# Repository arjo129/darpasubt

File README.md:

# net/batman-doc
Document all things related to batman.

## Network Bridges
A network bridge is a virtual cable, that connects two network interfaces.

By default, OpenWrt puts `eth0` and `wlan0` on the same bridge. This allows
connections on `wlan0` to connect over `eth0`. If `eth0` is connected to the
internet, then `wlan0` is connected to the internet.
```
root@OpenWrt:~# brctl show
bridge name     bridge id               STP enabled     interfaces
br-lan          7fff.b827eb551e8a       no              eth0
                                                        wlan0
```

## SSH over IPv6
It is possible to SSH from device A into an IPv6 device B, if batman is running 
on device B. I suspect this is because a layer 2 protocol needs to be running 
in order for SSH over IPv6 to work.

The SSH command is:
```
ssh -6 <user>@<device B address>%<device A interface>
```

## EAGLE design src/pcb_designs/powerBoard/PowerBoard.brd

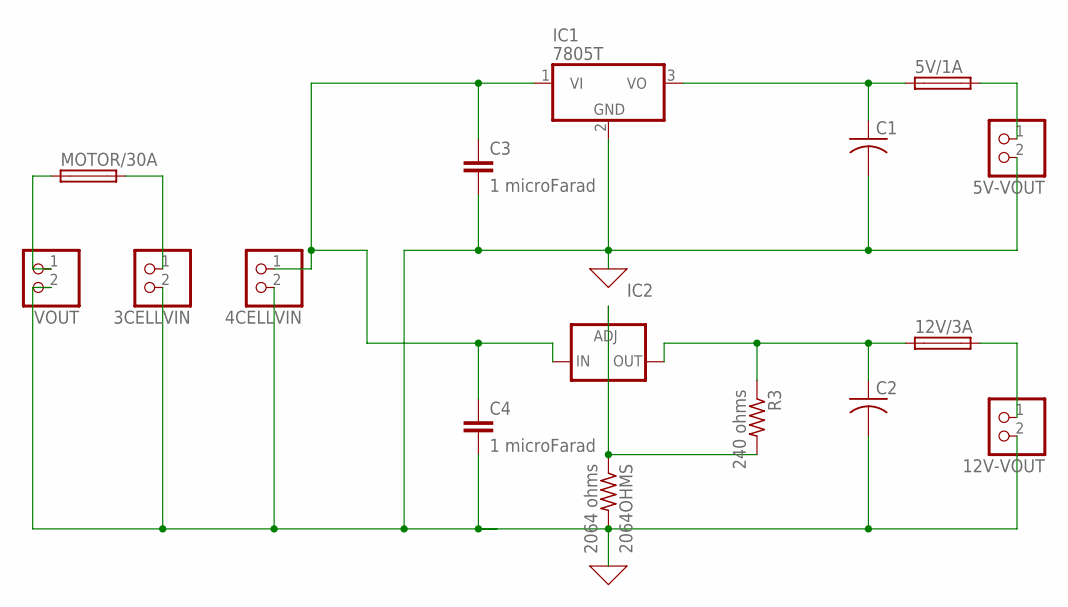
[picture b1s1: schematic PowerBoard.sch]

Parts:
3CELLVIN, 4CELLVIN, 5V-VOUT, 12V-VOUT: JST_2PIN-THM; JST-PH-2-THM
5V/1A, 12V/3A: GSH15
2064OHMS: 2064 ohms; 0805-THM
C1, C2: C-US050-035X075; C050-035X075
C3, C4: 1 microFarad; C5B2.5
IC1: 7805T; TO220H
IC2: LM337TS; 337TS
MOTOR/30A: GSH15
R3: 240 ohms; 0805-THM
VOUT: JST_2PIN-THM; JST-PH-2-THM

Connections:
0: 3CELLVIN.2 (1), 4CELLVIN.2 (1), 5V-VOUT.2 (1), 12V-VOUT.2 (1), 2064OHMS.2, C1.2, C2.2, C3.2, C4.2, IC1.2 (GND), VOUT.2 (1)
3CELLVIN: 3CELLVIN.1 (2), MOTOR/30A.2
unnamed: 5V/1A.1, C1.1, IC1.3 (VO)
unnamed: 5V-VOUT.1 (2), 5V/1A.2
unnamed: 12V/3A.1, C2.1, IC2.3 (OUT), R3.1
unnamed: 2064OHMS.1, IC2.1 (ADJ), R3.2
unnamed: 12V-VOUT.1 (2), 12V/3A.2
unnamed: MOTOR/30A.1, VOUT.1 (2)
unnamed: 4CELLVIN.1 (2), C3.1, C4.1, IC1.1 (VI), IC2.2 (IN)

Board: 2 copper layers, 16 parts (0 on the bottom side), 9 nets, no tracks yet.

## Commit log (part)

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2018-12-30 Improve frame format
    Use separate frame format for distance frames sent from the anchors.
    Reduce the array size for anchor response frames.
2019-01-01 added depthopticalflow
2019-01-01 Add reception of data from RX buffer
    Ability to receive and read date from RX buffer of the nRF52832 chip.
    Up to 20 bytes of data could be read from the RX buffer. The data is
    read into an array of unsigned chars where the Tag application will
    decode the data according to a common data format.
    The data format will have to be thoughtfully constructed, WIP.
2019-01-02 added tmux config... Customize as you please
2019-01-02 Add controller application for Tag/Anchor
    A simple Python script to act as a controller for the devices.
2019-01-03 Employ state transition
    We use state transition as a task management technique, replacing the
    previous task management technique which is just checking if the
    device should run measurement ranging.
    There are 5 states to each device:
    1. Received command from host device (terminal, UART, etc.)
    2. Standby (Device does nothing)
2019-01-04 Add ability to interrupt Anchor polling
    When the device operates in Anchor mode, the device is set to poll
    continuously for an initiation message without timeout.
    This commit adds an interrupt flag in order to jump out of that poll
    mode when a key is pressed so the device can process a command.
2019-01-05 Fix UART reception
    The 'app_uart_evt_t' event type 'APP_UART_DATA_READY' is triggered
    for EVERY BYTE that is moved into the buffer.
    Hence, we use a character (';' in this case) to represent the end of
    a transmission message. For every byte of data received, we check if
    this byte is the end character. If it is, we know the message has
    ended and so we notify the main application of incoming command.
2019-01-05 Modify Tag/Anchor application
    Tag and Anchor application now have it's ID set by the commands from
    the host device.
    Add a Gateway flag to determine if the device is Gateway node or not.
    This is to support the command distribution code in future.
2019-01-08 Add ability to interpret and execute system cmd
    When a system command is received, it can now be interpreted and executed.
2019-01-08 Add wait for system command function
    When the device that is not a gateway node, the device polls for a
    system command from the gateway node.
2019-01-09 Added probability distribution... and skeleton for test
2019-01-09 Add function to execute system commands
2019-01-12 Improve controller application
    Improve the keyboard interrupt of controller application.
    Use interrupt callbacks instead of a boolean flag.
    Replace usage of readline() with read() so there is better control
    of reading of bytes from the serial port.
    Add 2 more function to the controller:
    1. Start network ranging
2019-01-16 gitignore
2019-01-18 Remove unused functions code
2019-01-22 Replace sys command string with command construct
2019-01-23 Change delay to begin ranging for Tag
2019-01-24 added additional docs
2019-01-25 Removed old localization.py
2019-01-31 Updated .gitignore
2019-02-01 added travis CI hope it works
2019-02-01 minor changes in travis yml hopefully it builds
2019-02-02 Reduce range delay
    Overall delay for each ranging is now reduced to approximately
    ~1 second.
2019-02-02 Use TX to RX turn around for better sync
    When anchor finish transmitting distance, a TX to RX turn around is
    enabled. This is to ensure the first few anchors does not receive
    the later anchor's distance transmissions.
2019-02-02 Reduce timeout delay
2019-02-08 Added testing specific directories
2019-02-08 Cartographer tests
2019-02-09 Added point cloud output from cartographer
2019-02-12 Added joystick teleop
2019-02-21 Define constants
2019-02-21 Rename and move functions out of entry function
2019-02-22 Edit some comments
2019-02-23 Removed pycache
2019-02-24 Add dw_sleeper module
    dw_sleeper puts DW1000 device to SLEEP mode as well as wake up.
2019-02-26 Store rxId if is request
2019-02-27 Disable FreeRTOS
    FreeRTOS is currently causing a lot of issues when trying to work
    with the nRF app_timer library and DW1000 SLEEP feature.
    Disable it for now.
2019-02-27 Lower SPI speed from 8MHz to 2MHz
    This is to allow proper waking up from SLEEP mode.
2019-02-27 Add skeleton for protocol sequence
    The issue is that some messages are not transmitted out.
    Could it be that the intervals are too short? See source code.
2019-02-28 Expand time buffer
    Three timestamps per protocol cycle
2019-02-28 Copy received data into buffers
    Resolve types
2019-02-28 Increase MSG_LENGTH
2019-02-28 Move global variables into dedicated section
2019-02-28 Shrink time buffer
    Undo c823446, store two timestamps per node
2019-02-28 Add basic protocol sequence of transmissions
    Basic sequence of transmissions to follow protocol specifications.
2019-02-28 Turn on RX during range cycle
2019-02-28 Fix typo
2019-02-28 memcpy 2 instead of 3 timestamps
2019-02-28 Abstract out num of timestamps stored per node
2019-02-28 Describe elems of data in msg_template
2019-02-28 Abstract out data as input
2019-03-01 Rename functions
2019-03-01 Split setTimestamps into two functions
    First sets the 1st field of the ith transmitting node.
    Second sets the 1st field of the ith transmitting node.
2019-03-01 Specify that functions handle transmission
2019-03-01 Define buffer for times stamped by others
2019-03-01 Clean up docs
2019-03-01 Remove pointer offsets from arguments
    Offset should be determined by the caller,
    not determined by the function.
2019-03-01 Added navigation package
2019-03-04 Fix late turning on of receiver
    Issue:
    At the start of every cycle, all nodes other than 'master' node 0
    turns on their receiver to look for node 0's TX. However, due to
    delay in the turning on of receiver, the nodes will miss node 0's
    first transmission.
    Fix:
2019-03-04 Set delayed txtime before tx2 timer starts
2019-03-05 Modify goToSleep() for more flexible usage
2019-03-05 Call correct API for 32-bit ints
2019-03-05 Add new field to msg_template
    Whether msg is first transmission or not
2019-03-05 Add main.h header file
2019-03-07 Remove git symbols
2019-03-07 Write function prototypes
2019-03-07 Remove MsgType
2019-03-07 Fix timer and interrupt clashes #25
    This fix attempts to correct the clash that occurs between the master
    node's sleeping event and last slave node's ((N-1)th node) second TX.
    This is due to the fact that the timer values are calculated such
    that both will occur at the same time.
    Fix:
    One additional interval is added to the active period for every
2019-03-07 Add comment decriptions
2019-03-10 Remove unused code chunks
2019-03-11 Type time buffers as uint32
2019-03-13 Add message_template module
    This module handles the data structure to track timestamps and
    conversion of message_template struct to and from array.
2019-03-13 Fix description of data field
2019-03-13 Add macro for timestamp positions index
2019-03-13 Update comment
2019-03-14 Copy ts to table
2019-03-14 Remove updateTableRx
2019-03-15 Bring tableIndex out of range on last store
2019-03-15 Refactor table init and fix usage of updateTable
2019-03-15 Add common header file
2019-03-15 Remove unused function
2019-03-15 Refactor constants to use macros
2019-03-15 Fix using wrong value for array access
2019-03-17 Remove tableIndexes
    tableIndexes is no longer needed, removing all functions and
    references related.
2019-03-20 Retrieve from correct column and row in table
2019-03-27 Fix synchronising issues
2019-03-28 Remove old message_template folder
2019-03-28 Change to timestamp type to uint64
2019-03-29 Fix spacing
2019-04-01 Fix the memcpy length
2019-04-01 Use timestamper functions
2019-04-03 Reduce RX timeout buffer duration
2019-04-04 Fix RX_TX_BUFFER value to accomodate transition
2019-04-09 Replace DWM1000 user manual with newer version
2019-04-09 Test working configurations
    Basic testing of working configurations. Results in comments.
2019-04-09 Change comments
2019-04-11 Add distance measurement code
2019-04-11 Improve printing of output data
2019-04-12 Add Grove LoRa RF98 433 MHz code
2019-04-13 Refactor to reduce dependency
    Refactor several files to reduce dependency on common.h header.
2019-04-15 Refactor Server class to use initialisation list
2019-04-17 Read UART to start new set of measurements
2019-05-26 added the visualization for @lekoook to try out.
2019-06-10 power board pcb design
2019-06-13 Remove old vehicle controller
2019-06-13 Remove files due to mistake
2019-06-19 Add new datasheet for LIS2DH12 accelerometer
2019-06-19 Add new datasheet on calibration
2019-06-20 Fix doubles not printing properly
    stdio.h is required to print doubles.
2019-06-21 Refactor message_transceiver
2019-06-21 Refactor interrupt service routine functions
2019-06-22 Add README
2019-06-22 Add scripts
2019-06-23 Add bat0 to bridge
2019-06-23 Add bat0 del script
2019-06-23 Add prints, move prints around
2019-06-24 Differentiate messages with markers
2019-07-08 Use repeated timer to track cycle
2019-07-10 Remove unnecessary code
2019-07-12 Describe network bridges
2019-07-25 Add new STM32F407VG MCU project for motor
    New VSCode/PlatformIO project for developing motor firmware on the
    STM32F407VG MCU.
2019-07-25 Remove unnecessary build files
2019-07-27 Add PID speed control library
2019-07-30 Working on other GPIO port pins for PWM
2019-07-30 Remove unnecessary file
2019-08-05 Add more instances for all motors control
2019-08-08 Try usart
2019-08-12 Add steering solver
2019-08-20 Fix TwistSolver
2019-08-23 Change gitignore
2019-08-23 Separate Twist solving from rosserial callback
2019-08-28 Change inner arc turn solver
    Inner arc turn solver now solves for when the pivot point intersects
    the wheel-ground contact point.
2019-08-28 Compute platform halves
2019-08-30 Fix TwistSolver and add servo calibration
2019-09-05 Add holonomic movement solver
2019-09-06 Fix holonomic strafing angle errors
2019-09-07 Simplify arc movement calculation
2019-09-09 Remove unnecessary functions
2019-09-17 Optimize passing of structs into parameters
2019-09-17 Slight changes to main.cpp
2019-09-18 Add setting PID gain values on the fly
2019-09-20 Modify parameters for new motors
    New motors have a higher encoder to output shaft gear ratio of
    98.78:1 as compared to the previous ratio of 20.4.
    Thus, we change the SHAFT_TO_ENCODER_FACTOR in TwistSolver.h to the
    new value. This is to ensure the correct encoder speed is computed
    for pid control.
2019-09-28 Adjust servo calibration
2019-10-01 Remove calling of teleop.launch
2019-10-02 Clean up repo
    Remove unnecessary and move some files around
2019-10-04 Increase the motor speed limit
2019-10-22 Create LED_CONTROL
2019-11-27 Remove bin files
2019-11-27 Add TODO comment
2019-12-11 Allow sending and reassembly of Segments
2019-12-12 Add include guards and move some files
2019-12-13 Add ability to retransmit failed Chunks
2019-12-13 Add some descriptions and TODOs
2019-12-13 Fix wrong assignment of Chunk ID from Segment
2019-12-13 Modify #defines for HARDWARE SERIAL
2019-12-15 Fix Chunk ID generation
    The wrong way was used to determine the maximum value of the id given
    it's variable type. The fix uses limits.h from avr lib.
2019-12-26 Add Teensy 4.0 build environment config
2019-12-27 Change CRC lib used to FastCRC
